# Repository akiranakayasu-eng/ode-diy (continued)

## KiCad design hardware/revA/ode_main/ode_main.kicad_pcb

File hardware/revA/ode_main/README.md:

# ode_main — 自作 ODE（Art-Net → DMX512 2 ポート）rev A

ENTTEC ODE Mk2 の代わりに使う Art-Net / sACN → DMX ノード。miseru との [WebSocket 仕様](../../../docs/websocket-spec.md)に合わせる。（ENTTEC・ODE は ENTTEC 社の商標で、このプロジェクトは ENTTEC 社と関係がない）
ポートは 2 つ分の場所があり、初回は 1 ポートだけ実装してもよい（ポート 2 は後付け）。

## 状態（2026-11-23）

- 回路図: ERC 0、ネット照合 0。PCB rev A（100 × 84 mm、4 層）: DRC エラー 0 / 未接続 0、回路図との不一致 0
- JLCPCB で基板を作り、DMX 1 系統だけを手で実装した 1 台が動いている（2026-11-10 立ち上げ、[記録](docs/実機立ち上げ記録_2026-11-10.md)）。ファーム v0.2.0 で Ethernet・画面・WebSocket・Art-Net・sACN・DMX 出力を実機で確認済み
- 発注前レビュー: docs/PCBレビュー_2026-10-25.md
- ガーバー: ode_main_revA_gerber.zip（JLCPCB 用、4 層）
- 部品リスト: 部品リスト_revA.md、店ごとの買い物リスト 買い物リスト_revA.md
- **実装時の注意**: F1 は基板のパッドが 1206 だが、買い物リストの秋月 113955 PICOSMDC110S-2 は 0805。はんだを多めにして付けた（1206 の 0ZCJ0110FF2E なら合う）。ほかの代替部品は[立ち上げ記録](docs/実機立ち上げ記録_2026-11-10.md)の「実装時の注意・代替部品」

## 構成

| 部分 | 部品 | 内容 |
|---|---|---|
| MCU | U1 STM32F407VGT6（LQFP-100） | Ethernet MAC + LwIP で Art-Net を受ける。管理画面（HTTP / WebSocket）もここ |
| PHY / RJ45 | U3 LAN8742A + Y2 25MHz、J5 RJMG1BD3B8K1ANR | sacn_node_main と同じ回路（RMII、REF_CLK を PHY から出す） |
| 電源 | J1 USB-C（5V シンク、CC 5.1k）、U5 USBLC6、F1 PTC 1.1A、Q1 AO3401A 突入制限、U6 AP7361C-33E | 5V → +3V3。ADM2587E は +5V 直接 |
| DMX 出力 | U11 / U21 ADM2587E（絶縁 2.5kV）、U7 / U8 / U9 74AHCT1G125（3.3→5V） | XLR3 メス（J11 / J21）と JST XH 3P（J12 / J22）を並列。1 = GND、2 = Data−、3 = Data+ |
| MAC | U4 24AA02E48 | EUI-48 入り EEPROM |
| 操作 | SW1 RESET、SW2 LOCK、LED PWR / LOCK / STAT | LOCK ボタンを押したまま電源を入れると IP と PIN を初期値に戻す |
| 書き込み | J3 SWD 10 ピン、USB DFU（PA11 / PA12、JP1 = BOOT0）、J4 UART | |

### MCU ピン割り当て

| 機能 | ピン |
|---|---|
| DMX TX1 / TX2 | PE0 / PE1（タイマ起動の DMA で GPIO へ。sacn_node と同じ方式） |
| DE（2 ポート共通、10k プルダウン） | PD7 |
| RMII | PA1 REF_CLK, PA2 MDIO, PA7 CRS_DV, PC1 MDC, PC4 RXD0, PC5 RXD1, PB11 TX_EN, PB12 TXD0, PB13 TXD1, PB14 PHY nRST |
| USB | PA11 D−, PA12 D+ |
| LED / ボタン | PC10 LOCK, PC11 STAT / PD4 LOCK ボタン |
| I2C1（EEPROM） | PB6 SCL, PB7 SDA |
| デバッグ | PA13 SWDIO, PA14 SWCLK, PB3 SWO, PA9 / PA10 USART1 |

## 既定の設定

- IP 192.168.1.223（固定。ボタンでの初期化でこの値に戻る）
- WebSocket の同時接続数の上限 = 機器としての上限（30、実機で確定）。超えたら 1013 で閉じる

## 作り直し方（docker の kicad 10）

```
python3 scripts/gen_sch.py                     # 回路図
cat scripts/_pcb_*.py ... > scripts/gen_pcb.py  # 分割した部品を連結（順番は _pcb_body, _netlist, _pcb_place, _pcb_build, _refs, _pcb_tail）
python3 scripts/gen_pcb.py --geom && python3 scripts/route.py && python3 scripts/gen_pcb.py
bash scripts/_fin.sh                           # DRC、verify_pcb、3D 図
bash scripts/gerb.sh                           # ガーバー zip
```

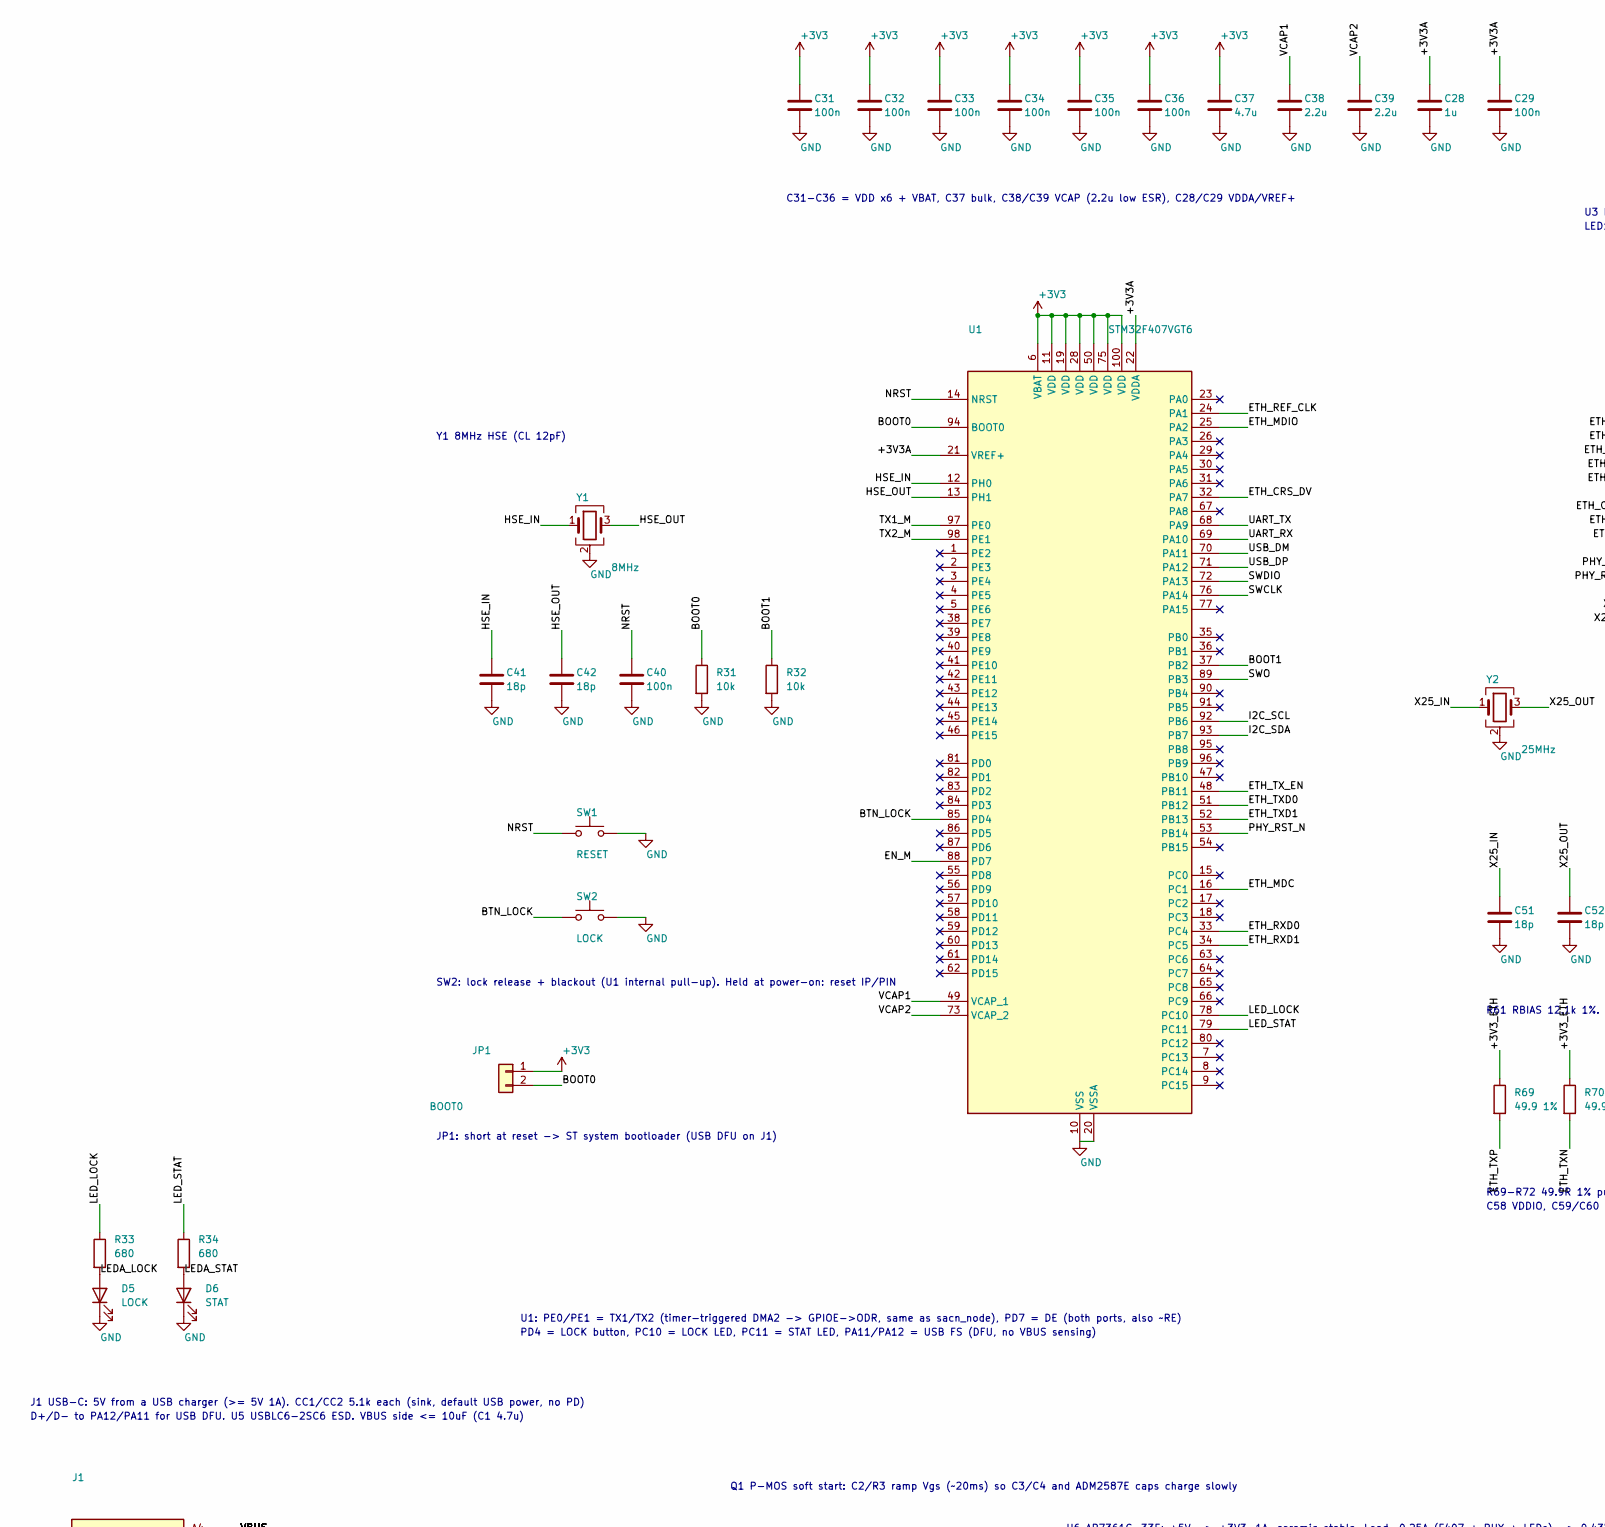
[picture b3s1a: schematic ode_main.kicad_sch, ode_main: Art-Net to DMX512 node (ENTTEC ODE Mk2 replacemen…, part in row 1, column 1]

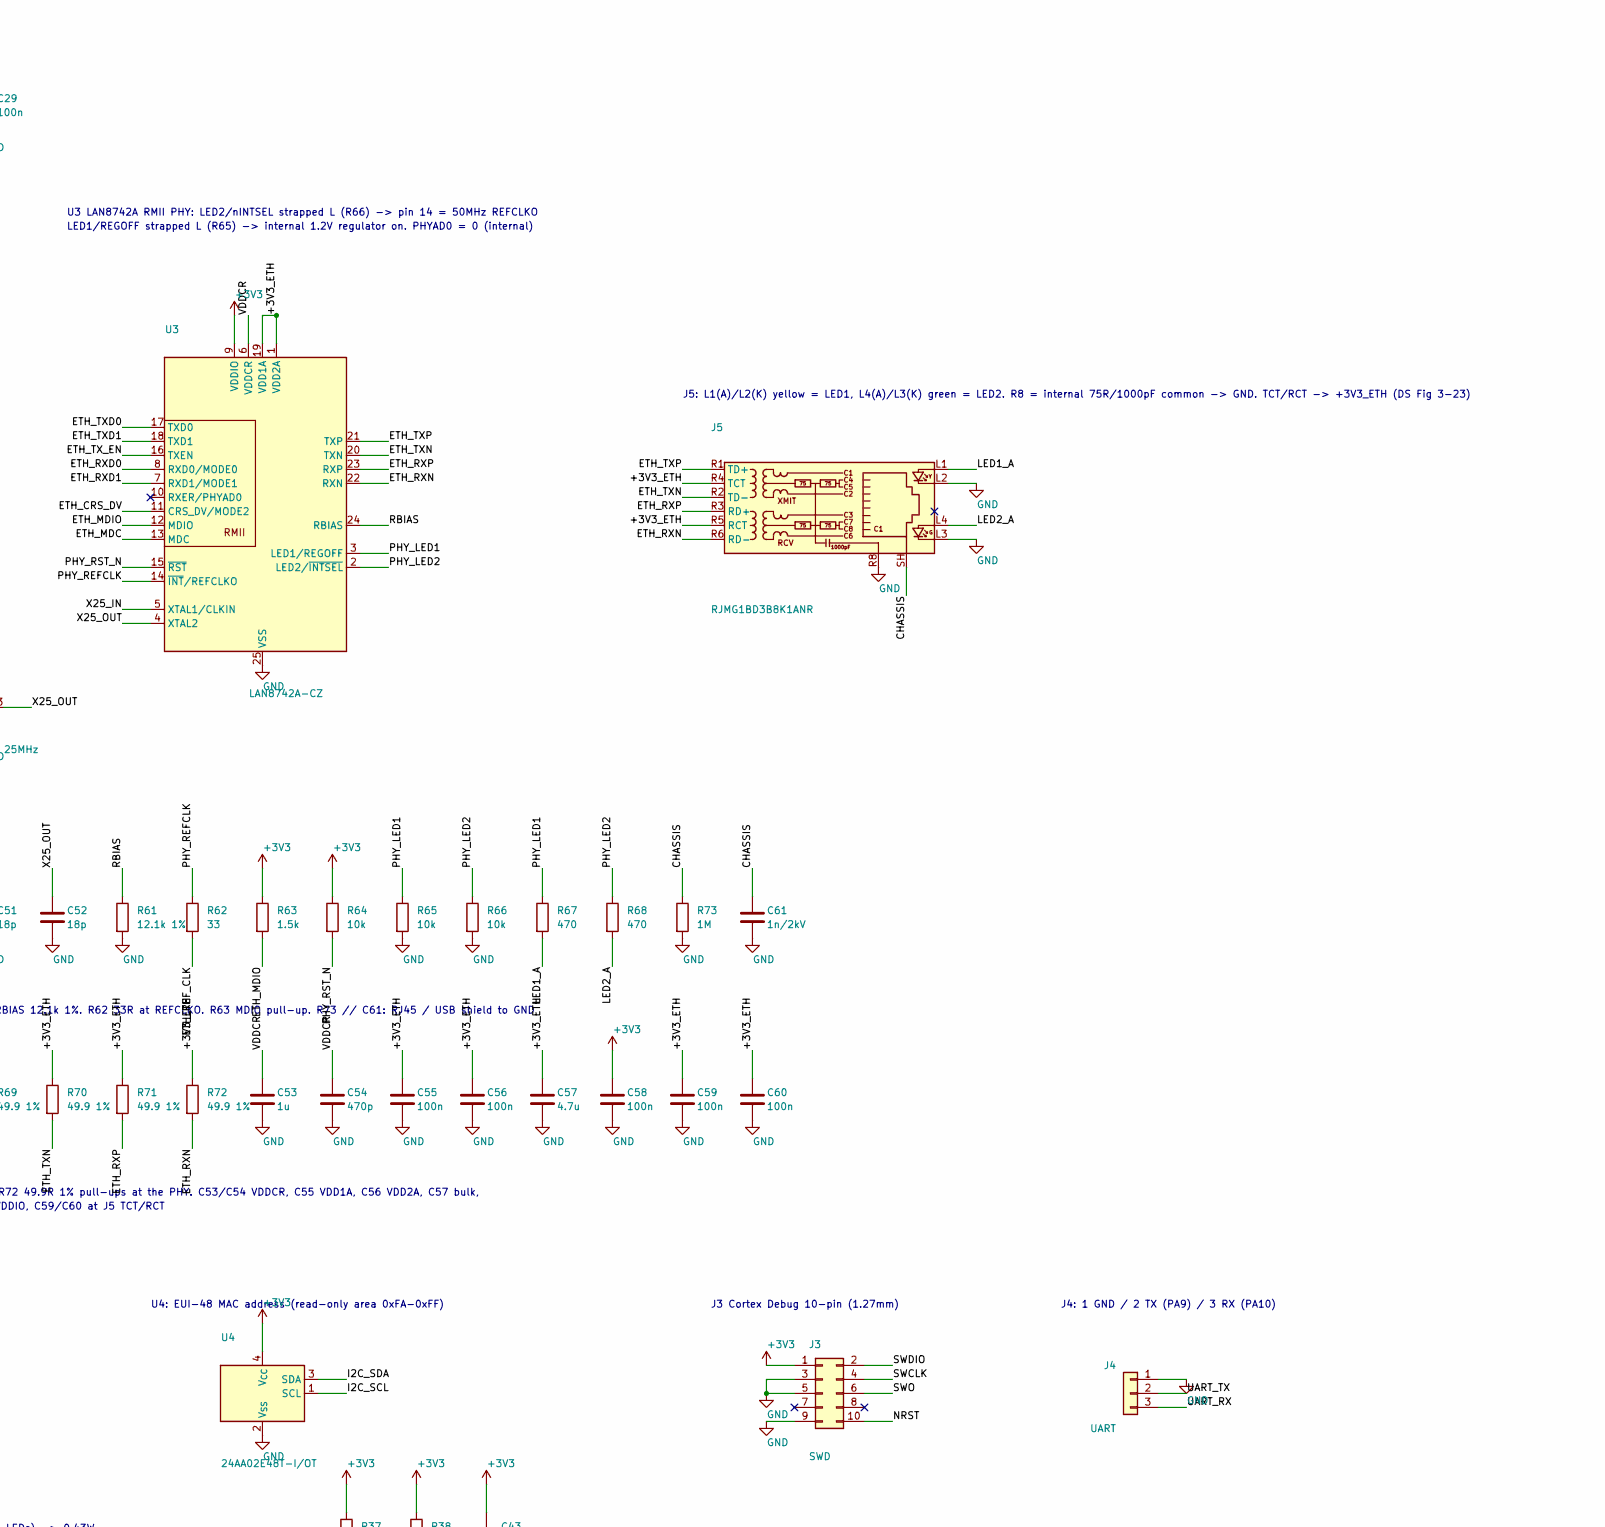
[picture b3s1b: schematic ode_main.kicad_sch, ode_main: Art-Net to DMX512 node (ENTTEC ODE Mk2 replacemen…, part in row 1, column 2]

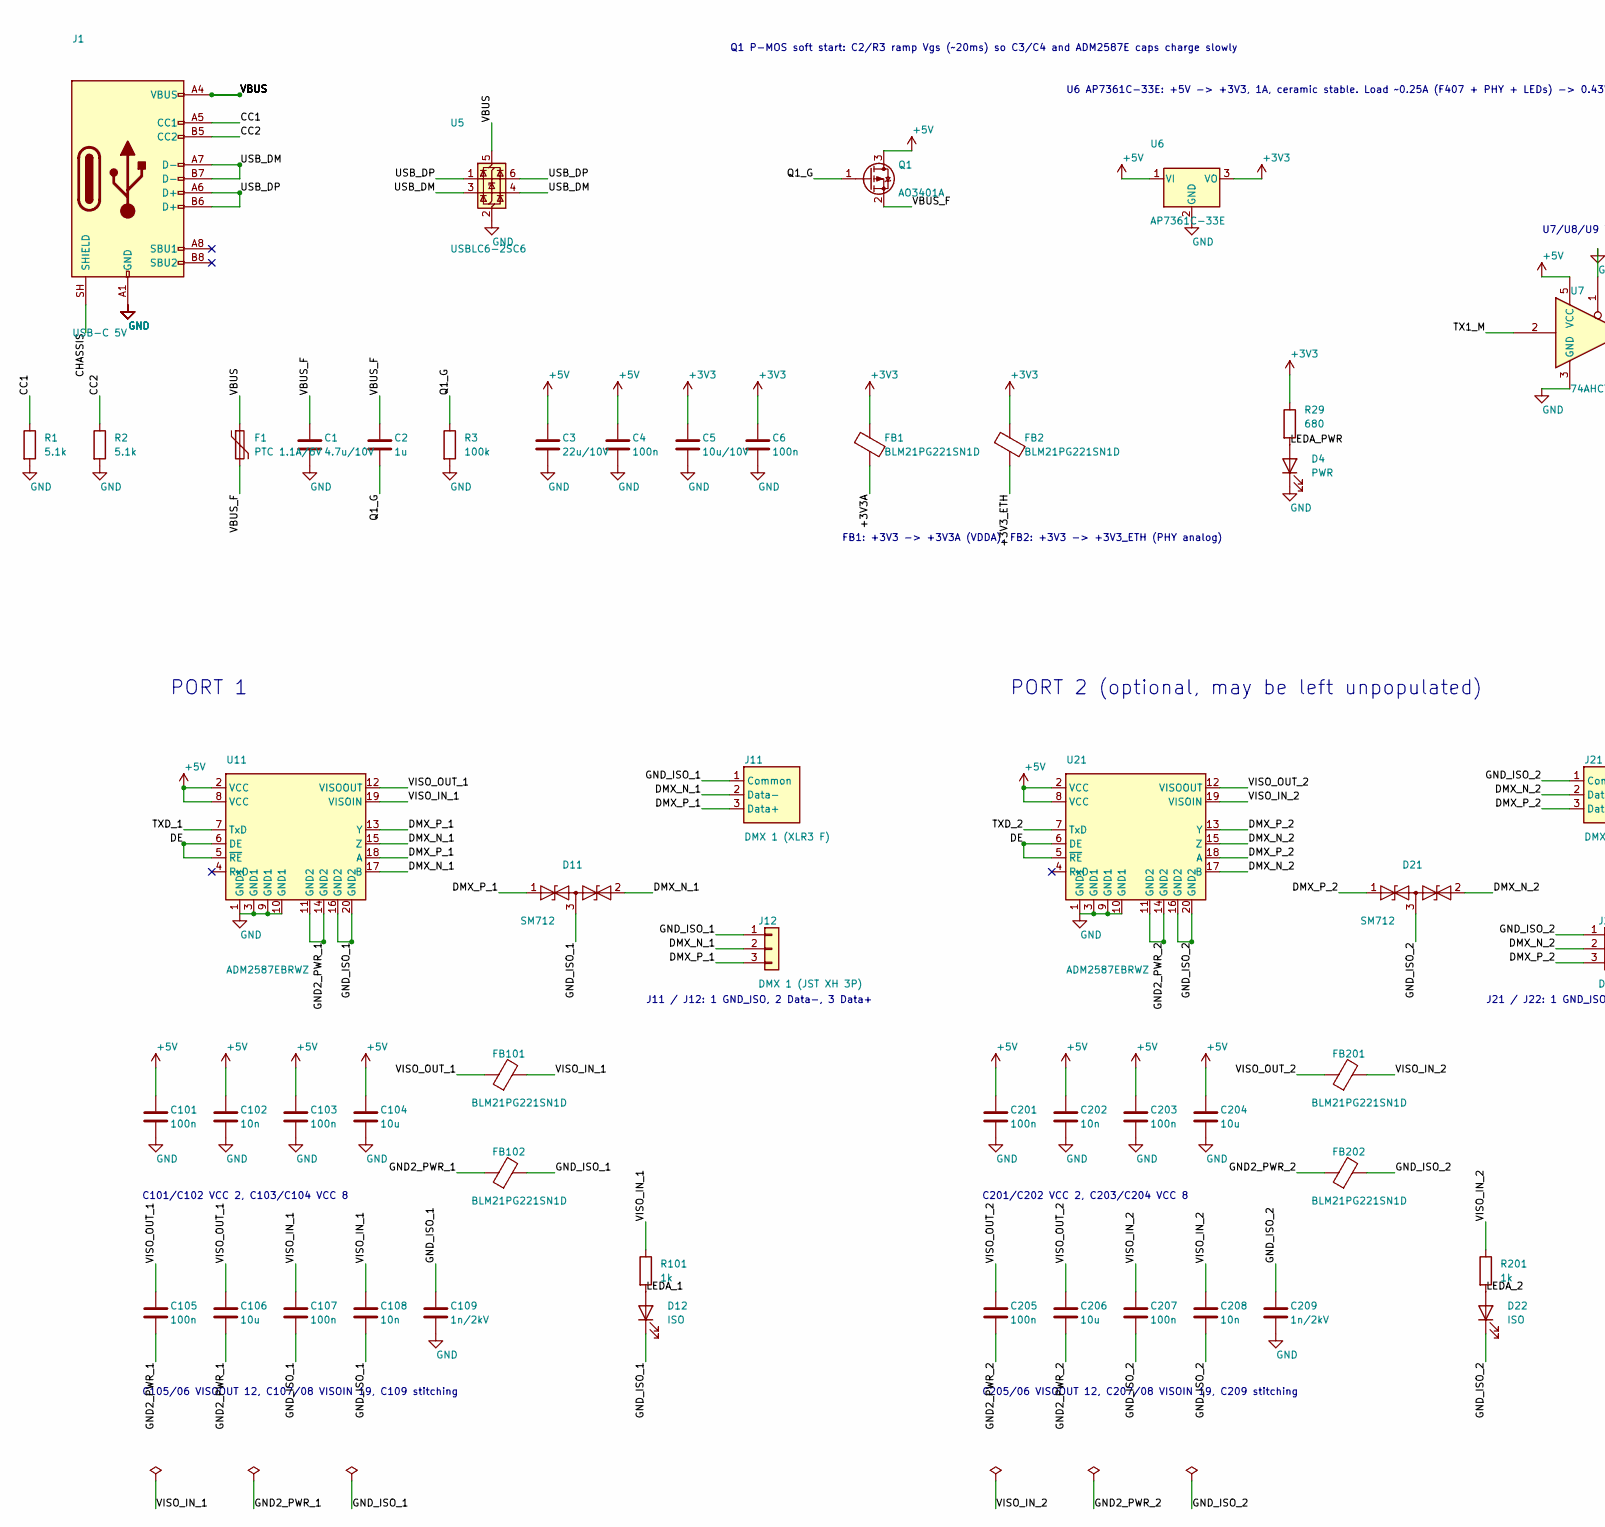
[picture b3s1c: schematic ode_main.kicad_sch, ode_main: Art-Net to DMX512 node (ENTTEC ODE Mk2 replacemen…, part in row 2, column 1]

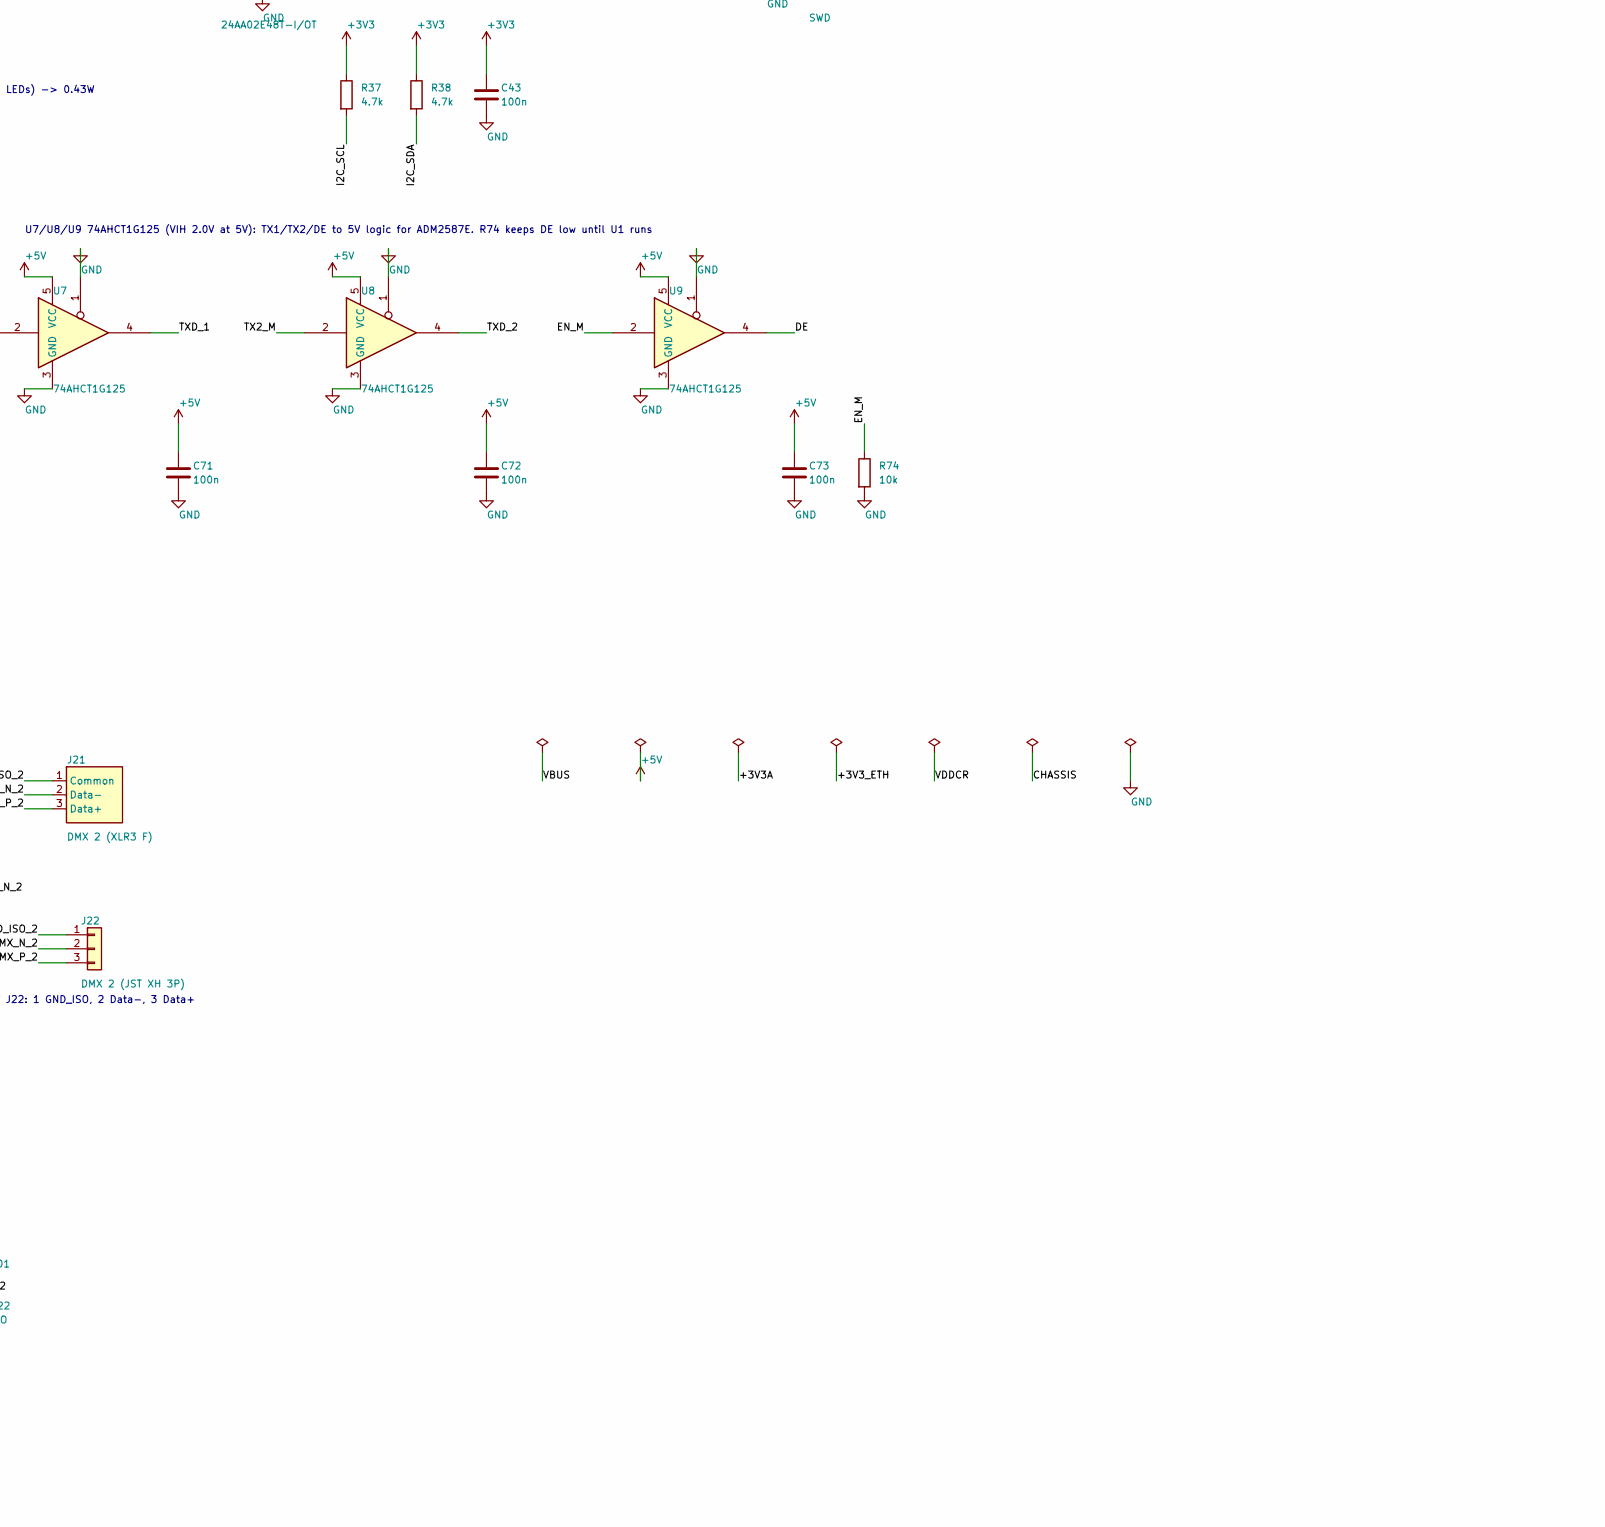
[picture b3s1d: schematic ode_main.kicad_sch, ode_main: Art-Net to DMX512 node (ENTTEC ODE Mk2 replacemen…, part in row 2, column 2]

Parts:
C1: 4.7u/10V; C_0805_2012Metric_Pad1.18x1.45mm_HandSolder
C2, C28, C53: 1u; C_0805_2012Metric_Pad1.18x1.45mm_HandSolder
C3: 22u/10V; C_1210_3225Metric_Pad1.33x2.70mm_HandSolder
C4, C6, C29, C31, C32, C33, C34, C35, C36, C40, C43, C55, C56, C58, C59, C60, C71, C72, C73, C101, C103, C105, C107, C201, C203, C205, C207: 100n; C_0805_2012Metric_Pad1.18x1.45mm_HandSolder
C5: 10u/10V; C_1210_3225Metric_Pad1.33x2.70mm_HandSolder
C37, C57: 4.7u; C_0805_2012Metric_Pad1.18x1.45mm_HandSolder
C38, C39: 2.2u; C_0805_2012Metric_Pad1.18x1.45mm_HandSolder
C41, C42, C51, C52: 18p; C_0805_2012Metric_Pad1.18x1.45mm_HandSolder
C54: 470p; C_0805_2012Metric_Pad1.18x1.45mm_HandSolder
C61, C109, C209: 1n/2kV; C_1206_3216Metric_Pad1.33x1.80mm_HandSolder
C102, C108, C202, C208: 10n; C_0805_2012Metric_Pad1.18x1.45mm_HandSolder
C104, C106, C204, C206: 10u; C_0805_2012Metric_Pad1.18x1.45mm_HandSolder
D4: PWR; LED_0805_2012Metric_Pad1.15x1.40mm_HandSolder
D5: LOCK; LED_0805_2012Metric_Pad1.15x1.40mm_HandSolder
D6: STAT; LED_0805_2012Metric_Pad1.15x1.40mm_HandSolder
D11, D21: SM712; SOT-23
D12, D22: ISO; LED_0805_2012Metric_Pad1.15x1.40mm_HandSolder
F1: PTC 1.1A/6V; Fuse_1206_3216Metric_Pad1.42x1.75mm_HandSolder
FB1, FB2, FB101, FB102, FB201, FB202: BLM21PG221SN1D; L_0805_2012Metric_Pad1.05x1.20mm_HandSolder
J1: USB-C 5V; USB_C_Receptacle_HRO_TYPE-C-31-M-12
J3: SWD; PinHeader_2x05_P1.27mm_Vertical
J4: UART; PinHeader_1x03_P2.54mm_Vertical
J5: RJMG1BD3B8K1ANR; RJ45_Amphenol_RJMG1BD3B8K1ANR
J11: DMX 1 (XLR3 F); Jack_XLR_Neutrik_NC3FAH_Horizontal
J12: DMX 1 (JST XH 3P); JST_XH_B3B-XH-A_1x03_P2.50mm_Vertical
J21: DMX 2 (XLR3 F); Jack_XLR_Neutrik_NC3FAH_Horizontal
J22: DMX 2 (JST XH 3P); JST_XH_B3B-XH-A_1x03_P2.50mm_Vertical
JP1: BOOT0; PinHeader_1x02_P2.54mm_Vertical
Q1: AO3401A; SOT-23
R1, R2: 5.1k; R_0805_2012Metric_Pad1.20x1.40mm_HandSolder
R3: 100k; R_0805_2012Metric_Pad1.20x1.40mm_HandSolder
R29, R33, R34: 680; R_0805_2012Metric_Pad1.20x1.40mm_HandSolder
R31, R32, R64, R65, R66, R74: 10k; R_0805_2012Metric_Pad1.20x1.40mm_HandSolder
R37, R38: 4.7k; R_0805_2012Metric_Pad1.20x1.40mm_HandSolder
R61: 12.1k 1%; R_0805_2012Metric_Pad1.20x1.40mm_HandSolder
R62: 33; R_0805_2012Metric_Pad1.20x1.40mm_HandSolder
R63: 1.5k; R_0805_2012Metric_Pad1.20x1.40mm_HandSolder
R67, R68: 470; R_0805_2012Metric_Pad1.20x1.40mm_HandSolder
R69, R70, R71, R72: 49.9 1%; R_0805_2012Metric_Pad1.20x1.40mm_HandSolder
R73: 1M; R_0805_2012Metric_Pad1.20x1.40mm_HandSolder
R101, R201: 1k; R_0805_2012Metric_Pad1.20x1.40mm_HandSolder
SW1: RESET; SW_SPST_TL3342
SW2: LOCK; SW_SPST_TL3342
U1: STM32F407VGT6; LQFP-100_14x14mm_P0.5mm
U3: LAN8742A-CZ; VQFN-24-1EP_4x4mm_P0.5mm_EP2.5x2.5mm_ThermalVias
U4: 24AA02E48T-I/OT; SOT-23-5
U5: USBLC6-2SC6; SOT-23-6
U6: AP7361C-33E; SOT-223-3_TabPin2
U7, U8, U9: 74AHCT1G125; SOT-23-5
U11, U21: ADM2587EBRWZ; SOIC-20W_7.5x12.8mm_P1.27mm
Y1: 8MHz; Crystal_SMD_3225-4Pin_3.2x2.5mm
Y2: 25MHz; Crystal_SMD_3225-4Pin_3.2x2.5mm

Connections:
+3V3: C5.1, C6.1, C31.1, C32.1, C33.1, C34.1, C35.1, C36.1, C37.1, C43.1, C58.1, FB1.1, FB2.1, J3.1, JP1.1, R29.1, R37.1, R38.1, R63.1, R64.1, U1.6 (VBAT), U1.11 (VDD), U1.19 (VDD), U1.28 (VDD), U1.50 (VDD), U1.75 (VDD), U1.100 (VDD), U3.9 (VDDIO), U4.4 (V_{CC}), U6.3 (VO)
+5V: C3.1, C4.1, C71.1, C72.1, C73.1, C101.1, C102.1, C103.1, C104.1, C201.1, C202.1, C203.1, C204.1, Q1.3 (D), U6.1 (VI), U7.5 (VCC), U8.5 (VCC), U9.5 (VCC), U11.2 (VCC), U11.8 (VCC), U21.2 (VCC), U21.8 (VCC)
/+3V3A: C28.1, C29.1, FB1.2, U1.21 (VREF+), U1.22 (VDDA)
/+3V3_ETH: C55.1, C56.1, C57.1, C59.1, C60.1, FB2.2, J5.R4 (TCT), J5.R5 (RCT), R69.1, R70.1, R71.1, R72.1, U3.1 (VDD2A), U3.19 (VDD1A)
/BOOT0: JP1.2, R31.1, U1.94 (BOOT0)
/BOOT1: R32.1, U1.37 (PB2)
/BTN_LOCK: SW2.1, U1.85 (PD4)
/CC1: J1.A5 (CC1), R1.1
/CC2: J1.B5 (CC2), R2.1
/CHASSIS: C61.1, J1.SH (SHIELD), J5.SH, R73.1
/DE: U9.4, U11.5 (~RE), U11.6 (DE), U21.5 (~RE), U21.6 (DE)
/DMX_N_1: D11.2 (A2), J11.2 (Data-), J12.2, U11.15 (Z), U11.17 (B)
/DMX_N_2: D21.2 (A2), J21.2 (Data-), J22.2, U21.15 (Z), U21.17 (B)
/DMX_P_1: D11.1 (A1), J11.3 (Data+), J12.3, U11.13 (Y), U11.18 (A)
/DMX_P_2: D21.1 (A1), J21.3 (Data+), J22.3, U21.13 (Y), U21.18 (A)
/EN_M: R74.1, U1.88 (PD7), U9.2
/ETH_CRS_DV: U1.32 (PA7), U3.11 (CRS_DV/MODE2)
/ETH_MDC: U1.16 (PC1), U3.13 (MDC)
/ETH_MDIO: R63.2, U1.25 (PA2), U3.12 (MDIO)
/ETH_REF_CLK: R62.2, U1.24 (PA1)
/ETH_RXD0: U1.33 (PC4), U3.8 (RXD0/MODE0)
/ETH_RXD1: U1.34 (PC5), U3.7 (RXD1/MODE1)
/ETH_RXN: J5.R6 (RD-), R72.2, U3.22 (RXN)
/ETH_RXP: J5.R3 (RD+), R71.2, U3.23 (RXP)
/ETH_TXD0: U1.51 (PB12), U3.17 (TXD0)
/ETH_TXD1: U1.52 (PB13), U3.18 (TXD1)
/ETH_TXN: J5.R2 (TD-), R70.2, U3.20 (TXN)
/ETH_TXP: J5.R1 (TD+), R69.2, U3.21 (TXP)
/ETH_TX_EN: U1.48 (PB11), U3.16 (TXEN)
/GND2_PWR_1: C105.2, C106.2, FB102.1, U11.11 (GND2), U11.14 (GND2)
/GND2_PWR_2: C205.2, C206.2, FB202.1, U21.11 (GND2), U21.14 (GND2)
/GND_ISO_1: C107.2, C108.2, C109.1, D11.3 (common), D12.1 (K), FB102.2, J11.1 (Common), J12.1, U11.16 (GND2), U11.20 (GND2)
/GND_ISO_2: C207.2, C208.2, C209.1, D21.3 (common), D22.1 (K), FB202.2, J21.1 (Common), J22.1, U21.16 (GND2), U21.20 (GND2)
/HSE_IN: C41.1, U1.12 (PH0), Y1.1
/HSE_OUT: C42.1, U1.13 (PH1), Y1.3
/I2C_SCL: R37.2, U1.92 (PB6), U4.1 (SCL)
/I2C_SDA: R38.2, U1.93 (PB7), U4.3 (SDA)
/LED1_A: J5.L1, R67.2
/LED2_A: J5.L4, R68.2
/LEDA_1: D12.2 (A), R101.2
/LEDA_2: D22.2 (A), R201.2
/LEDA_LOCK: D5.2 (A), R33.2
/LEDA_PWR: D4.2 (A), R29.2
/LEDA_STAT: D6.2 (A), R34.2
/LED_LOCK: R33.1, U1.78 (PC10)
/LED_STAT: R34.1, U1.79 (PC11)
/NRST: C40.1, J3.10, SW1.1, U1.14 (NRST)
/PHY_LED1: R65.1, R67.1, U3.3 (LED1/REGOFF)
/PHY_LED2: R66.1, R68.1, U3.2 (LED2/~INTSEL)
/PHY_REFCLK: R62.1, U3.14 (~INT/REFCLKO)
/PHY_RST_N: R64.2, U1.53 (PB14), U3.15 (~RST)
/Q1_G: C2.2, Q1.1 (G), R3.1
/RBIAS: R61.1, U3.24 (RBIAS)
/SWCLK: J3.4, U1.76 (PA14)
/SWDIO: J3.2, U1.72 (PA13)
/SWO: J3.6, U1.89 (PB3)
/TX1_M: U1.97 (PE0), U7.2
/TX2_M: U1.98 (PE1), U8.2
/TXD_1: U7.4, U11.7 (TxD)
/TXD_2: U8.4, U21.7 (TxD)
/UART_RX: J4.3, U1.69 (PA10)
/UART_TX: J4.2, U1.68 (PA9)
/USB_DM: J1.A7 (D-), J1.B7 (D-), U1.70 (PA11), U5.3 (I/O2), U5.4 (I/O2)
/USB_DP: J1.A6 (D+), J1.B6 (D+), U1.71 (PA12), U5.1 (I/O1), U5.6 (I/O1)
/VBUS: F1.1, J1.A4 (VBUS), J1.A9 (VBUS), J1.B4 (VBUS), J1.B9 (VBUS), U5.5 (VBUS)
/VBUS_F: C1.1, C2.1, F1.2, Q1.2 (S)
/VCAP1: C38.1, U1.49 (VCAP_1)
/VCAP2: C39.1, U1.73 (VCAP_2)
/VDDCR: C53.1, C54.1, U3.6 (VDDCR)
/VISO_IN_1: C107.1, C108.1, FB101.2, R101.1, U11.19 (VISOIN)
/VISO_IN_2: C207.1, C208.1, FB201.2, R201.1, U21.19 (VISOIN)
/VISO_OUT_1: C105.1, C106.1, FB101.1, U11.12 (VISOOUT)
/VISO_OUT_2: C205.1, C206.1, FB201.1, U21.12 (VISOOUT)
/X25_IN: C51.1, U3.5 (XTAL1/CLKIN), Y2.1
/X25_OUT: C52.1, U3.4 (XTAL2), Y2.3
GND: C1.2, C3.2, C4.2, C5.2, C6.2, C28.2, C29.2, C31.2, C32.2, C33.2, C34.2, C35.2, C36.2, C37.2, C38.2, C39.2, C40.2, C41.2, C42.2, C43.2, C51.2, C52.2, C53.2, C54.2, C55.2, C56.2, C57.2, C58.2, C59.2, C60.2, C61.2, C71.2, C72.2, C73.2, C101.2, C102.2, C103.2, C104.2, C109.2, C201.2, C202.2, C203.2, C204.2, C209.2, D4.1 (K), D5.1 (K), D6.1 (K), J1.A1 (GND), J1.A12 (GND), J1.B1 (GND), J1.B12 (GND), J3.3, J3.5, J3.9, J4.1, J5.L2, J5.L3, J5.R8, R1.2, R2.2, R3.2, R31.2, R32.2, R61.2, R65.2, R66.2, R73.2, R74.2, SW1.2, SW2.2, U1.10 (VSS), U1.20 (VSSA), U1.27 (VSS), U1.74 (VSS), U1.99 (VSS), U3.25 (VSS), U4.2 (V_{SS}), U5.2 (GND), U6.2 (GND), U7.1, U7.3 (GND), U8.1, U8.3 (GND), U9.1, U9.3 (GND), U11.1 (GND1), U11.3 (GND1), U11.9 (GND1), U11.10 (GND1), U21.1 (GND1), U21.3 (GND1), U21.9 (GND1), U21.10 (GND1), Y1.2 (G), Y1.4 (G), Y2.2 (G), Y2.4 (G)

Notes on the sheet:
U1: PE0/PE1 = TX1/TX2 (timer-triggered DMA2 -> GPIOE->ODR, same as sacn_node), PD7 = DE (both ports, also ~RE)
PD4 = LOCK button, PC10 = LOCK LED, PC11 = STAT LED, PA11/PA12 = USB FS (DFU, no VBUS sensing)
C31-C36 = VDD x6 + VBAT, C37 bulk, C38/C39 VCAP (2.2u low ESR), C28/C29 VDDA/VREF+
Y1 8MHz HSE (CL 12pF)
SW2: lock release + blackout (U1 internal pull-up). Held at power-on: reset IP/PIN
JP1: short at reset -> ST system bootloader (USB DFU on J1)
U3 LAN8742A RMII PHY: LED2/nINTSEL strapped L (R66) -> pin 14 = 50MHz REFCLKO
LED1/REGOFF strapped L (R65) -> internal 1.2V regulator on. PHYAD0 = 0 (internal)
J5: L1(A)/L2(K) yellow = LED1, L4(A)/L3(K) green = LED2. R8 = internal 75R/1000pF common -> GND. TCT/RCT -> +3V3_ETH (DS Fig 3-23)
R61 RBIAS 12.1k 1%. R62 33R at REFCLKO. R63 MDIO pull-up. R73 // C61: RJ45 / USB shield to GND
R69-R72 49.9R 1% pull-ups at the PHY. C53/C54 VDDCR, C55 VDD1A, C56 VDD2A, C57 bulk,
C58 VDDIO, C59/C60 at J5 TCT/RCT
U4: EUI-48 MAC address (read-only area 0xFA-0xFF)
J3 Cortex Debug 10-pin (1.27mm)
J4: 1 GND / 2 TX (PA9) / 3 RX (PA10)
J1 USB-C: 5V from a USB charger (>= 5V 1A). CC1/CC2 5.1k each (sink, default USB power, no PD)
D+/D- to PA12/PA11 for USB DFU. U5 USBLC6-2SC6 ESD. VBUS side <= 10uF (C1 4.7u)
Q1 P-MOS soft start: C2/R3 ramp Vgs (~20ms) so C3/C4 and ADM2587E caps charge slowly
U6 AP7361C-33E: +5V -> +3V3, 1A, ceramic stable. Load ~0.25A (F407 + PHY + LEDs) -> 0.43W
FB1: +3V3 -> +3V3A (VDDA), FB2: +3V3 -> +3V3_ETH (PHY analog)
U7/U8/U9 74AHCT1G125 (VIH 2.0V at 5V): TX1/TX2/DE to 5V logic for ADM2587E. R74 keeps DE low until U1 runs
PORT 1
C101/C102 VCC 2, C103/C104 VCC 8
C105/06 VISOOUT 12, C107/08 VISOIN 19, C109 stitching
J11 / J12: 1 GND_ISO, 2 Data-, 3 Data+
PORT 2 (optional, may be left unpopulated)
C201/C202 VCC 2, C203/C204 VCC 8
C205/06 VISOOUT 12, C207/08 VISOIN 19, C209 stitching
J21 / J22: 1 GND_ISO, 2 Data-, 3 Data+

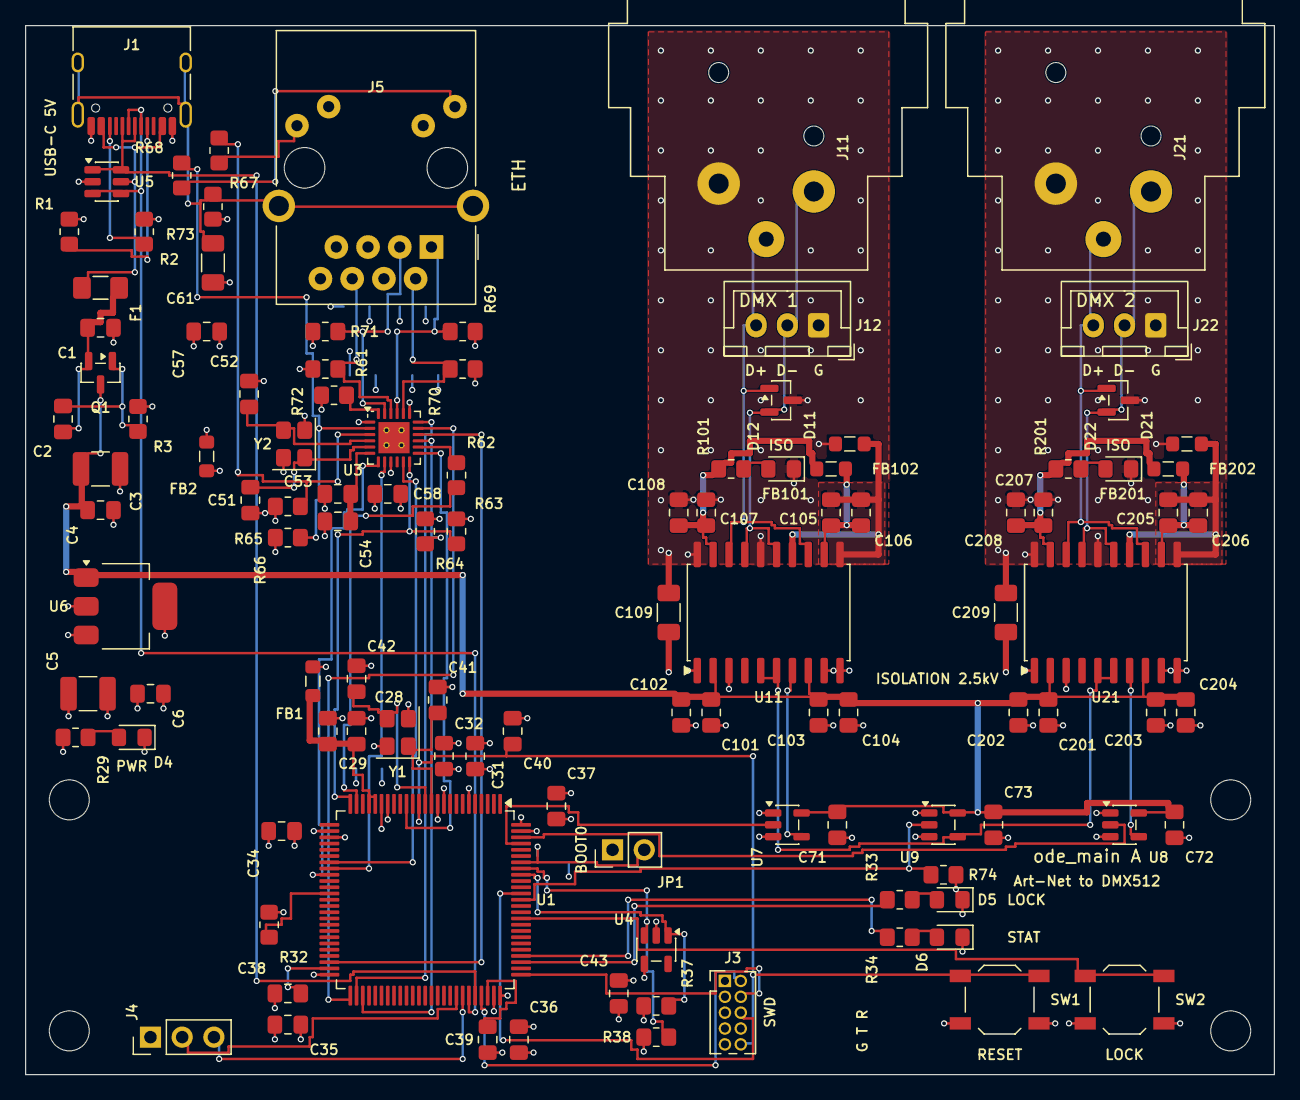
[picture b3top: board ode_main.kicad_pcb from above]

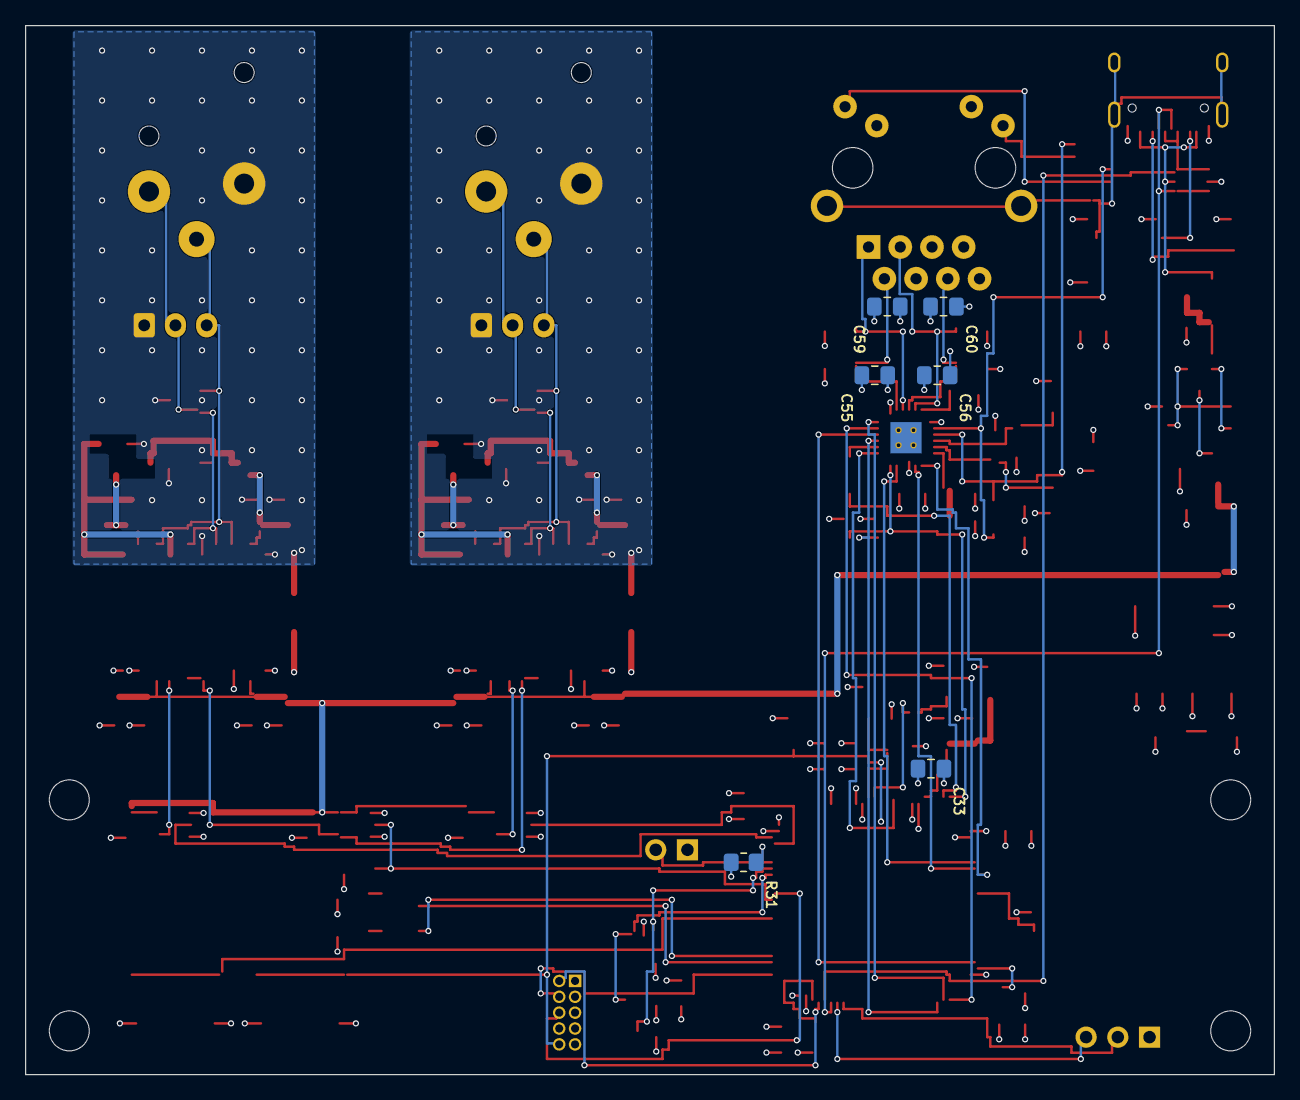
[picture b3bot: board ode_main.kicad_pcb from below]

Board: 4 copper layers, 100.0 x 84.0 mm, 121 parts (6 on the bottom side), 76 nets.

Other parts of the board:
H1, H2, H3, H4: MountingHole_3.2mm_M3

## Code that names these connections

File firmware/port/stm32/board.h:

/* ode_main rev A のピン割り当て（回路図 ode_main.kicad_sch / netlist.net から）
 *
 *   DMX TX1 / TX2   PE0 / PE1  → U7 / U8 74AHCT1G125 → U11 / U21 ADM2587E TxD（rev A は U8・U21 未実装）
 *   DE（送信許可）  PD7 EN_M   → U9 → ADM2587E DE と ~RE（R74 10k でプルダウン。High で送信）
 *   RMII            PA1 REF_CLK, PA2 MDIO, PA7 CRS_DV, PC1 MDC, PC4 RXD0, PC5 RXD1, PB11 TX_EN, PB12 TXD0, PB13 TXD1
 *   PHY nRST        PB14（R64 でプルアップ）。LAN8742A の PHYAD0 は未接続（内部プルダウン）→ アドレス 0
 *   LED             PC10 LOCK（D5）、PC11 STAT（D6）。High で点灯（680Ω → LED → GND）
 *   ボタン          PD4 LOCK（SW2 → GND、外付けプルアップなし → 内部プルアップ）
 *   EEPROM          PB6 SCL, PB7 SDA（U4 24AA02E48、MAC は 0xFA〜0xFF）
 *   UART            PA9 TX, PA10 RX（J4: 1 GND, 2 TX, 3 RX、115200bps 8N1、3.3V）
 *   HSE             8MHz（Y1）
 */
#ifndef BOARD_H
#define BOARD_H
#include "stm32f4xx.h"
#include <stdint.h>
#include <stdbool.h>

extern volatile uint32_t g_ms;

void board_dfu_check(void);           /* 目印があれば ROM の USB DFU へ飛ぶ（main の最初に呼ぶ） */
void board_clock_init(void);
void board_gpio_init(void);
void board_iwdg_init(void);
static inline void board_iwdg_kick(void) { IWDG->KR = 0xAAAA; }
bool board_button_raw(void);          /* 押されていれば true */
void board_led_stat(bool on);
void board_uart_init(void);
void board_log(const char *fmt, ...);
void board_delay_ms(uint32_t ms);

/* eth.c */
struct netif;
int  eth_init(struct netif *nif, const uint8_t mac[6]);   /* lwIP の netif_add に渡す初期化は eth_netif_init */
signed char eth_netif_init(struct netif *nif);
void eth_poll(struct netif *nif);       /* 受信をすべて lwIP に渡す */
void eth_link_poll(struct netif *nif);  /* 250ms ごとにリンクを見る */
extern uint16_t g_phy_id1, g_phy_id2;
extern int g_phy_addr;

/* dmx.c */
void dmx_init(void);
void dmx_set(const uint8_t *slots512);
extern volatile uint32_t g_dmx_frames;

/* flash_settings.c */
#include "settings.h"
bool flash_settings_load(settings_t *s);
void flash_settings_save(const settings_t *s);

/* mac_eeprom.c */
bool mac_eeprom_read(uint8_t mac[6]);
#endif

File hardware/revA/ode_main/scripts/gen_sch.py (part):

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"""ode_main.kicad_sch を生成する。

自作 ODE (ENTTEC ODE Mk2 の置き換え、Art-Net -> DMX512)。sacn_node_main を縮小した 1 枚基板。
  U1 STM32F407VGT6  Ethernet MAC + LwIP で Art-Net / HTTP / WebSocket を受け、DMX を PE0 (/PE1) から出す
                    (sacn_node と同じタイマ + DMA -> GPIOE->ODR。ファーム共通化のためピンも同じ)
  U3 LAN8742A       RMII PHY (sacn_node_main と同じ)
  J5 RJ45           Amphenol RJMG1BD3B8K1ANR
  J1 USB-C          5V 受電 (CC 5.1k x 2、PD なし)。D+/D- は PA12/PA11 (USB DFU 書き込み用)
  Q1 AO3401A        突入電流の緩和 (VBUS 側の容量を 10uF 以下にし、+5V の大容量はゲート RC でゆっくりつなぐ)
  U6 AP7361C-33E    +5V -> +3V3 LDO (1A、セラミック安定)
  ポート 1 / 2      ADM2587E 絶縁 (sacn_node_out8 / dmx_usb_pro と同じ周辺)、XLR3 + JST XH3 並列
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    # Ethernet RMII (sacn_node_main と同じ)
    "24": "ETH_REF_CLK", "25": "ETH_MDIO", "32": "ETH_CRS_DV", "16": "ETH_MDC", "33": "ETH_RXD0",
    "34": "ETH_RXD1", "48": "ETH_TX_EN", "51": "ETH_TXD0", "52": "ETH_TXD1", "53": "PHY_RST_N",
    # DMX (PE0 / PE1 = TX1 / TX2、PD8 = DE。sacn_node と同じピン)
    "97": "TX1_M", "98": "TX2_M", "88": "EN_M",
    # LED / スイッチ
    "78": "LED_LOCK", "79": "LED_STAT", "85": "BTN_LOCK",
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    # ---------------- U1 STM32F407VGT6
    part("U1", "STM32F407VGTx", "STM32F407VGT6", 203.2, 182.88, MCU, hside=20.0,
         direct=("27", "74", "99"), ref_off=(-20.32, -76.2), val_off=(5.08, -76.2))
    s.text((101.6, 287.02), "U1: PE0/PE1 = TX1/TX2 (timer-triggered DMA2 -> GPIOE->ODR, same as sacn_node), PD7 = DE (both ports, also ~RE)", 1.27)
    s.text((101.6, 289.56), "PD4 = LOCK button, PC10 = LOCK LED, PC11 = STAT LED, PA11/PA12 = USB FS (DFU, no VBUS sensing)", 1.27)
    row(66.04, 152.4, [("C31", "C", "100n", "+3V3", "GND"), ("C32", "C", "100n", "+3V3", "GND"),
                       ("C33", "C", "100n", "+3V3", "GND"), ("C34", "C", "100n", "+3V3", "GND"),
                       ("C35", "C", "100n", "+3V3", "GND"), ("C36", "C", "100n", "+3V3", "GND"),
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    part("J4", "Conn_01x03", "UART", 487.68, 299.72, {"1": "GND", "2": "UART_TX", "3": "UART_RX"},
         mirror=True, fp="Connector_PinHeader_2.54mm:PinHeader_1x03_P2.54mm_Vertical",
         ref_off=(-2.54, -5.08), val_off=(-2.54, 6.35))
    s.text((474.98, 284.48), "J4: 1 GND / 2 TX (PA9) / 3 RX (PA10)", 1.27)

    # ---------------- 電源: USB-C 5V -> +5V (突入緩和) -> +3V3
    USB = {"A4": "VBUS", "A9": "VBUS", "B4": "VBUS", "B9": "VBUS",
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    part("J1", "USB_C_Receptacle_USB2.0_16P", "USB-C 5V", 30.48, 340.36, USB, hside=8.0,
         ref_off=(-10.16, -25.4), val_off=(-10.16, 27.94))
    s.text((12.7, 302.26), "J1 USB-C: 5V from a USB charger (>= 5V 1A). CC1/CC2 5.1k each (sink, default USB power, no PD)", 1.27)
    s.text((12.7, 304.8), "D+/D- to PA12/PA11 for USB DFU. U5 USBLC6-2SC6 ESD. VBUS side <= 10uF (C1 4.7u)", 1.27)
    row(388.62, 12.7, [("R1", "R", "5.1k", "CC1", "GND"), ("R2", "R", "5.1k", "CC2", "GND")])
    part("U5", "USBLC6-2SC6", "USBLC6-2SC6", 96.52, 340.36,
         {"1": "USB_DP", "6": "USB_DP", "3": "USB_DM", "4": "USB_DM", "5": "VBUS", "2": "GND"}, hside=5.0,
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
